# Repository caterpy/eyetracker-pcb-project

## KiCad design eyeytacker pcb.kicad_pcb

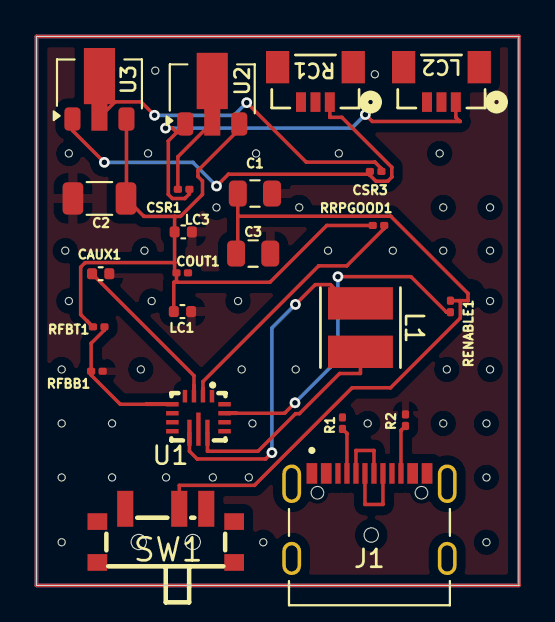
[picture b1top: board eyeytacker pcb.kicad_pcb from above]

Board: 2 copper layers, 26.8 x 30.5 mm, 23 parts (0 on the bottom side), 17 nets.

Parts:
C1, C3: 22uF; C_0805_2012Metric
C2: 47uF; C_1206_3216Metric
CAUX1: 100nF; C_0402_1005Metric
COUT1: 10uF; C_0201_0603Metric
CSR1, CSR3: 536; R_0201_0603Metric
J1: USB_C_Receptacle_USB2.0_16P; KINGHELM_KH-TYPE-C-16P
L1: 2.2uH; IND_WPN4020H_SNL
LC1, LC3: 100nF; C_0402_1005Metric
LC2: SM03B-SURS-TF; CONN3_SM03B-SURS_JST
R1, R2: 5.1k; R_0201_0603Metric
RC1: SM03B-SURS-TF; CONN3_SM03B-SURS_JST
RENABLE1: 10k; R_0201_0603Metric
RFBB1: 100k; R_0201_0603Metric
RFBT1: 845k; R_0201_0603Metric
RRPGOOD1: 100k; R_0201_0603Metric
SW1: SW_DPDT_x2; SW-SMD_MK-12C02-G020
U1: TPS63070RNMR; VQFN-HR-15_L3.0-W2.5-P0.50-BL_TPS63070RNMR
U2, U3: LM317L_SOT-89; SOT-89-3

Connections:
7.5VO: C2.1, COUT1.1, LC1.1, LC3.1, RFBT1.1, RRPGOOD1.2, U2.3 (VI), U3.3 (VI)
GND: C1.2, C2.2, C3.2, CAUX1.2, COUT1.2, LC1.2, LC2.2, LC3.2, R1.2, R2.2, RC1.2, RFBB1.2, U1.4 (GND), U1.6 (FB2), U1.10 (PGND)
IRO1: CSR3.2, RC1.1, U3.1 (ADJ)
IRO2: CSR1.2, LC2.1, U2.1 (ADJ)
unnamed: J1.A5 (CC1), R1.1
unnamed: J1.B5 (CC2), R2.1
unnamed: RENABLE1.1, U1.14 (EN)
unnamed: RFBB1.1, RFBT1.2, U1.5 (FB)
unnamed: L1.2, U1.11 (L1)
unnamed: L1.1, U1.9 (L2)
unnamed: RRPGOOD1.1, U1.2 (PG)
unnamed: CAUX1.1, U1.3 (VAUX)
unnamed: CSR1.1, U2.2 (VO)
unnamed: CSR3.1, U3.2 (VO)
USBO: C1.1, C3.1, RENABLE1.2, SW1.2 (B)
dn: J1.A7 (D-), J1.B7 (D-)
dp: J1.A6 (D+), J1.B6 (D+)
